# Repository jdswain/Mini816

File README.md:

# Mini816 (rev B)

This is the `v2` branch: rev B adds a floppy controller, moves the CPU
and flash to PLCC, drops TIM-Bus, and puts the external connectors along
the back edge for a case like the Atari ST (internal floppy drive and
keyboard). Rev A is on `main`.

A small 65C816 teaching computer: a gift kit for two first-year
computer science students. Through-hole parts throughout, for soldering
practice.

* W65C816S (PLCC-44 socket) at 7.3728 MHz, from a 14.7456 MHz oscillator
  divided in the CPLD
* 512K SRAM (AS6C4008-55) and 512K flash (SST39SF040, PLCC-32 socket): banks $00-$07
  RAM, $08-$0F flash. 128K parts fit the same sockets (see the Memory sheet
  for the RAM_SIZE jumper)
* ATF1504AS CPLD (PLCC-44 socket): bank latch, decode, strobes, clock
  generation and stretching for I/O cycles
* W65C22N VIA: 64-key keyboard on its own PCB (`../Mini816-Keyboard`),
  scanned through a 4-bit column select (PB0-PB2 + CA2) into a 74HC154 on
  the keyboard; Atari joystick (DE-9 on the keyboard PCB) on column 15; SD card over bit-banged SPI
  (microSD module); timer-1 sound; VDP interrupt on CB1, floppy interrupt on CB2
* Z85C30 SCC: two TTL serial ports on FTDI-style 6-pin headers; channel A
  takes a USB-C USB-serial module, which can also power the board
* TMS9118 video (NTSC composite, 256x192, 32 sprites) with two TMS4416
  VRAMs, driving a small composite LCD monitor
* Intel 82077AA floppy controller (PLCC-68 socket) at $C030, PC 34-pin
  drive header and 4-pin drive power header, for a 3.5" 720K/1.44M drive;
  no DMA (the CPU moves the data through the FIFO)
* 12 V barrel jack, metal toggle switch, Recom R-78K5.0-2.0 switching
  regulator (2 A, enough for the floppy drive) for 5 V; 12 V on a 2-pin header for the composite LCD. A jumper
  can instead take 5 V from the USB-serial module (bench use, no LCD)

All fine-pitch parts (USB, USB-serial chip, microSD socket) are on
plug-in modules, so the board itself is through-hole only.

Sheets: CPU, Memory, Logic, IO, Serial, Video, Floppy, Power. Each sheet
carries notes on its part of the design.

Symbols: `lib/65Parts.kicad_sym` is a copy of the 65-16 library;
`lib/Mini816.kicad_sym` holds the PLCC-44 and PDIP-40 W65C816S, W65C22 and Z85C30,
the TMS9118, TMS4416 and DS1813 (plus the now-unused ERM240128FS-2).

The CPLD pin assignment is on the Logic sheet; the Verilog must match it.

`docs/em16-profile.md` describes the machine for emulation (em16).

Board layout (rev B): 200 x 125 mm, 4 layers (inner 1 GND plane, inner 2
signals with a +5V pour). Back edge, left to right: 12 V jack, power
switch, LCD 12 V header, RCA video, SD module, serial A, serial B. Front
edge: keyboard ribbon header. Right edge: floppy drive header and drive
power. Four M3 mounting holes.

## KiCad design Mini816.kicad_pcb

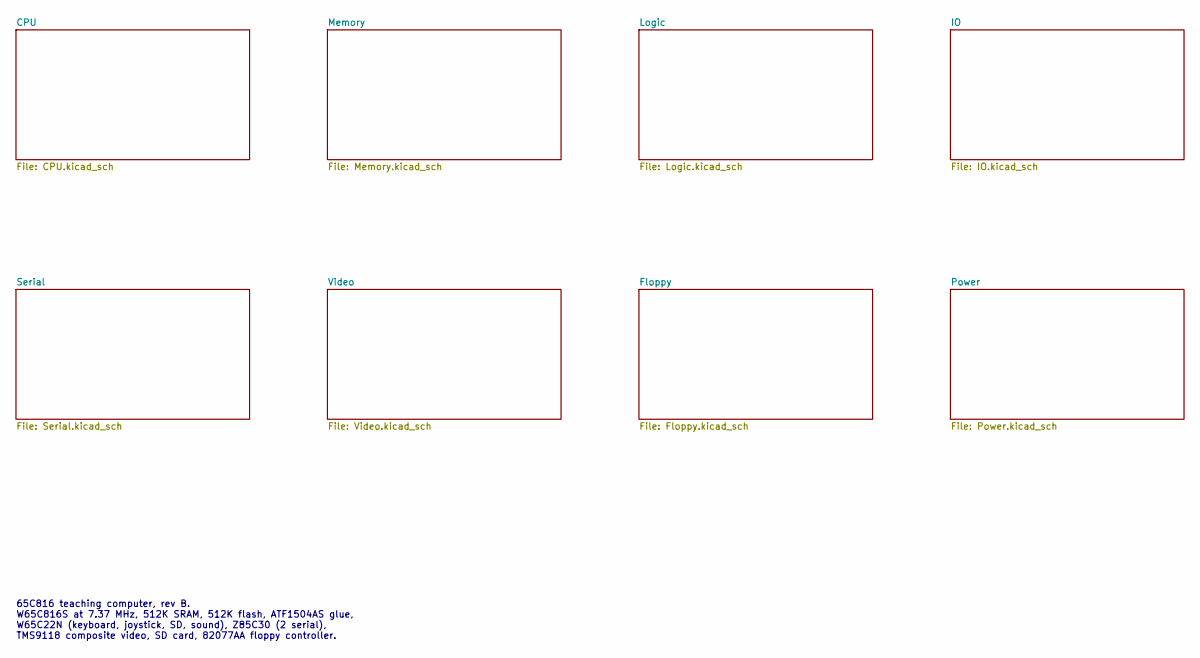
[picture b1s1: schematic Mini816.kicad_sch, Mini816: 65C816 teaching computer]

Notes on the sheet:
65C816 teaching computer, rev B. W65C816S at 7.37 MHz, 512K SRAM, 512K flash, ATF1504AS glue, W65C22N (keyboard, joystick, SD, sound), Z85C30 (2 serial), TMS9118 composite video, SD card, 82077AA floppy controller.

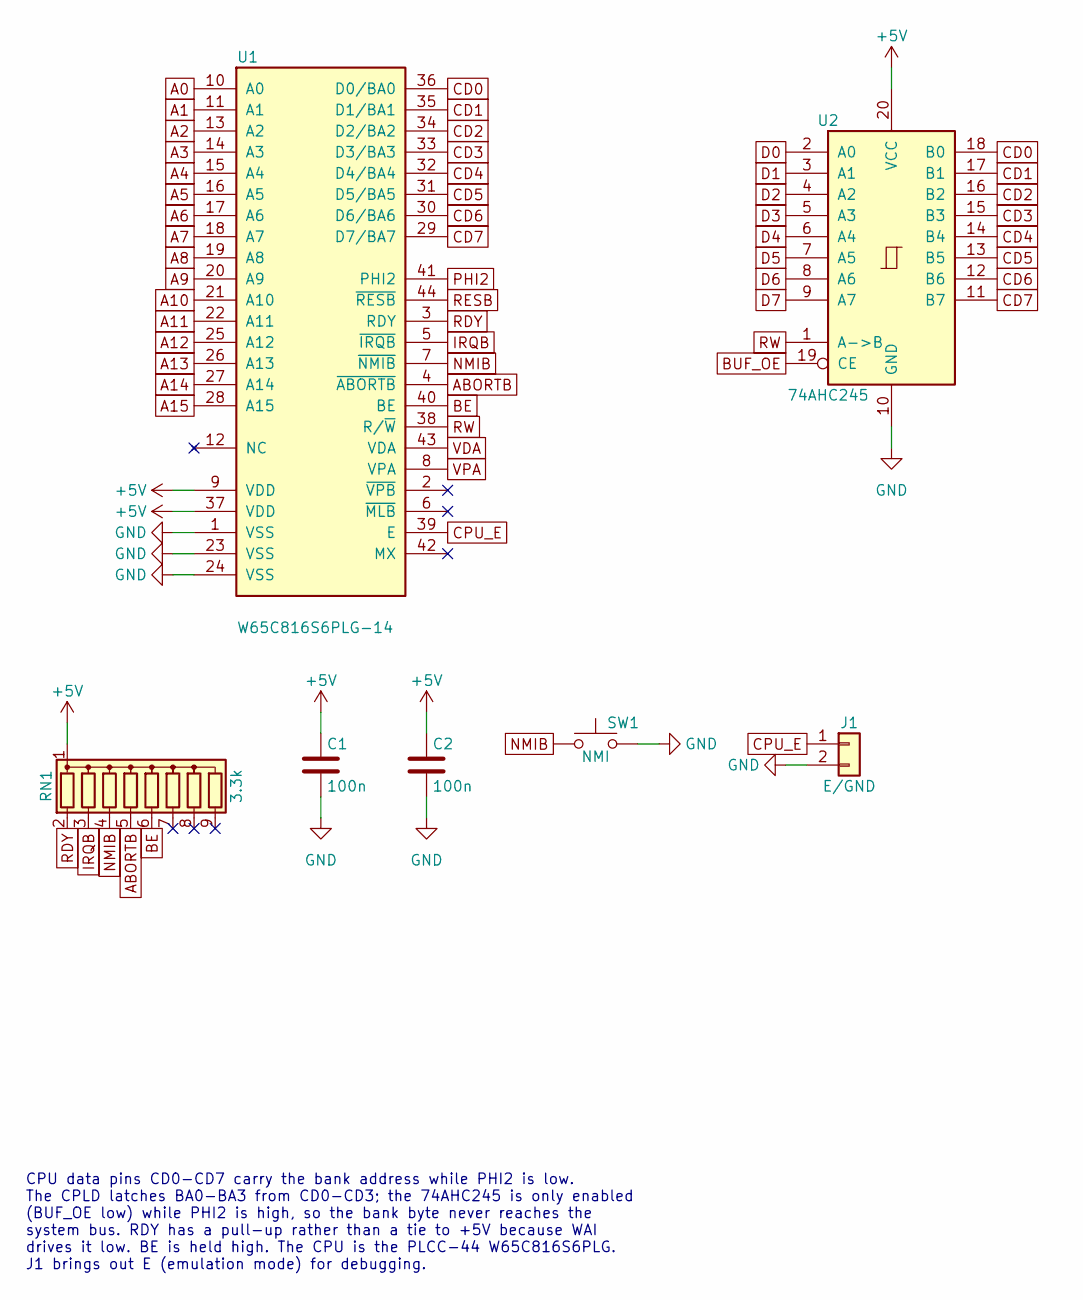
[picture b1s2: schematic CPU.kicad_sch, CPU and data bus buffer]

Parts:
C1, C2: 100n; C_Disc_D5.0mm_W2.5mm_P5.00mm
J1: E/GND; PinHeader_1x02_P2.54mm_Vertical
RN1: 3.3k; R_Array_SIP9
SW1: NMI; SW_PUSH_6mm
U1: W65C816S6PLG-14; PLCC-44_THT-Socket
U2: 74AHC245; DIP-20_W7.62mm_Socket

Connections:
+5V: C1.1, C2.1, RN1.1 (common), U1.9 (VDD), U1.37 (VDD), U2.20 (VCC); also elsewhere on the board
A0: U1.10 (A0); also elsewhere on the board
A1: U1.11 (A1); also elsewhere on the board
A2: U1.13 (A2); also elsewhere on the board
A3: U1.14 (A3); also elsewhere on the board
A4: U1.15 (A4); also elsewhere on the board
A5: U1.16 (A5); also elsewhere on the board
A6: U1.17 (A6); also elsewhere on the board
A7: U1.18 (A7); also elsewhere on the board
A8: U1.19 (A8); also elsewhere on the board
A9: U1.20 (A9); also elsewhere on the board
A10: U1.21 (A10); also elsewhere on the board
A11: U1.22 (A11); also elsewhere on the board
A12: U1.25 (A12); also elsewhere on the board
A13: U1.26 (A13); also elsewhere on the board
A14: U1.27 (A14); also elsewhere on the board
A15: U1.28 (A15); also elsewhere on the board
ABORTB: RN1.5 (R4), U1.4 (~ABORTB)
BE: RN1.6 (R5), U1.40 (BE)
BUF_OE: U2.19 (CE); also elsewhere on the board
CD0: U1.36 (D0/BA0), U2.18 (B0); also elsewhere on the board
CD1: U1.35 (D1/BA1), U2.17 (B1); also elsewhere on the board
CD2: U1.34 (D2/BA2), U2.16 (B2); also elsewhere on the board
CD3: U1.33 (D3/BA3), U2.15 (B3); also elsewhere on the board
CD4: U1.32 (D4/BA4), U2.14 (B4)
CD5: U1.31 (D5/BA5), U2.13 (B5)
CD6: U1.30 (D6/BA6), U2.12 (B6)
CD7: U1.29 (D7/BA7), U2.11 (B7)
CPU_E: J1.1, U1.39 (E)
D0: U2.2 (A0); also elsewhere on the board
D1: U2.3 (A1); also elsewhere on the board
D2: U2.4 (A2); also elsewhere on the board
D3: U2.5 (A3); also elsewhere on the board
D4: U2.6 (A4); also elsewhere on the board
D5: U2.7 (A5); also elsewhere on the board
D6: U2.8 (A6); also elsewhere on the board
D7: U2.9 (A7); also elsewhere on the board
GND: C1.2, C2.2, J1.2, SW1.2, U1.1 (VSS), U1.23 (VSS), U1.24 (VSS), U2.10 (GND); also elsewhere on the board
IRQB: RN1.3 (R2), U1.5 (~IRQB); also elsewhere on the board
NMIB: RN1.4 (R3), SW1.1, U1.7 (~NMIB)
PHI2: U1.41 (PHI2); also elsewhere on the board
RDY: RN1.2 (R1), U1.3 (RDY)
RESB: U1.44 (~RESB); also elsewhere on the board
RW: U1.38 (R/~W), U2.1 (A->B); also elsewhere on the board
VDA: U1.43 (VDA); also elsewhere on the board
VPA: U1.8 (VPA); also elsewhere on the board

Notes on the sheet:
CPU data pins CD0-CD7 carry the bank address while PHI2 is low. The CPLD latches BA0-BA3 from CD0-CD3; the 74AHC245 is only enabled (BUF_OE low) while PHI2 is high, so the bank byte never reaches the system bus. RDY has a pull-up rather than a tie to +5V because WAI drives it low. BE is held high. 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

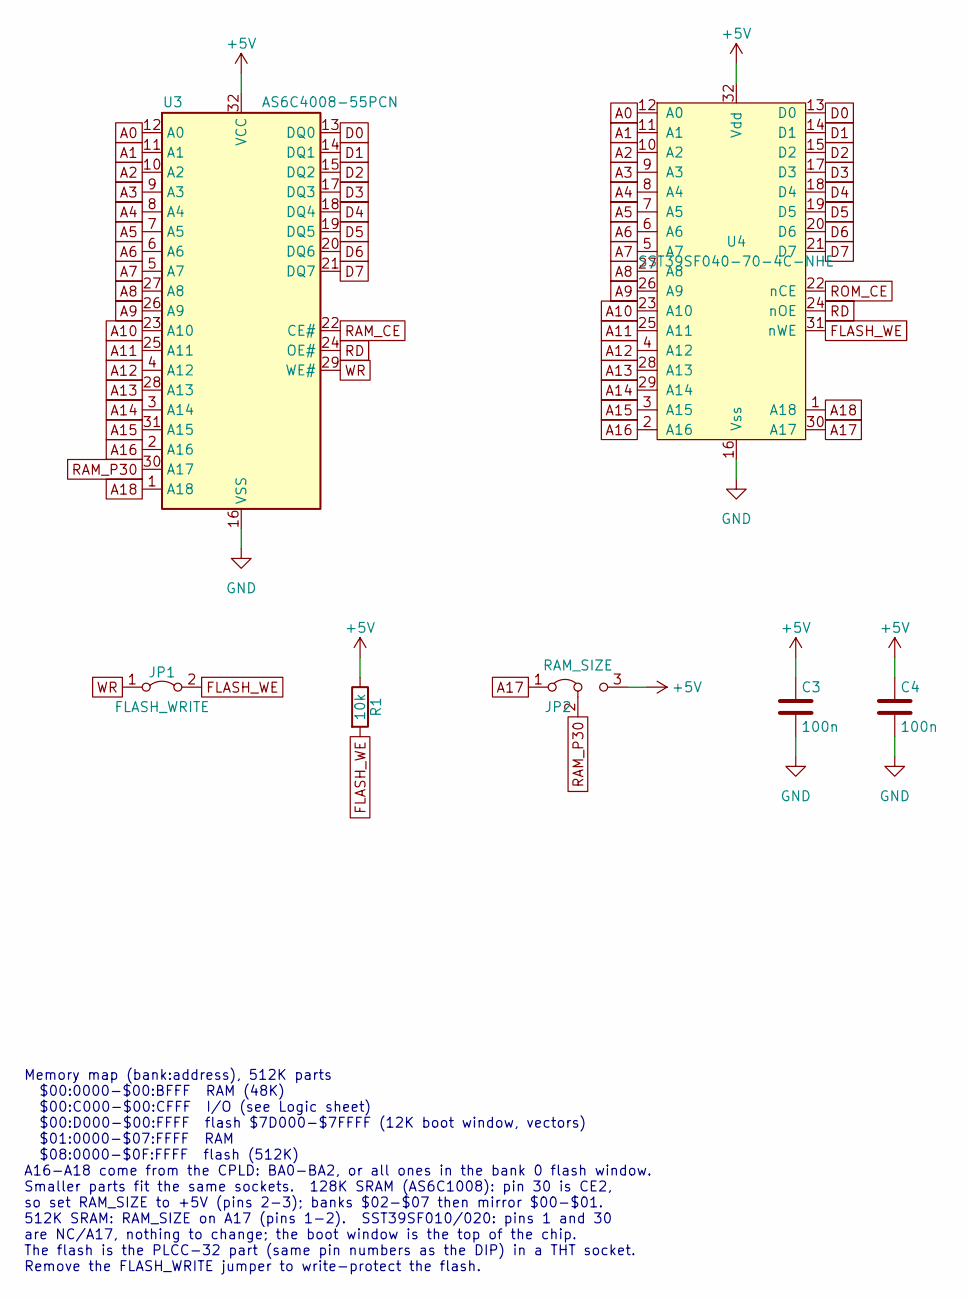
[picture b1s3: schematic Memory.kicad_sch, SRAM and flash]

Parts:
C3, C4: 100n; C_Disc_D5.0mm_W2.5mm_P5.00mm
JP1: FLASH_WRITE; PinHeader_1x02_P2.54mm_Vertical
JP2: RAM_SIZE; PinHeader_1x03_P2.54mm_Vertical
R1: 10k; R_Axial_DIN0207_L6.3mm_D2.5mm_P10.16mm_Horizontal
U3: AS6C4008-55PCN; DIP-32_W15.24mm_Socket
U4: SST39SF040-70-4C-NHE; PLCC-32_THT-Socket

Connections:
+5V: C3.1, C4.1, JP2.3 (B), R1.1, U3.32 (VCC), U4.32 (Vdd); also elsewhere on the board
A0: U3.12 (A0), U4.12 (A0); also elsewhere on the board
A1: U3.11 (A1), U4.11 (A1); also elsewhere on the board
A2: U3.10 (A2), U4.10 (A2); also elsewhere on the board
A3: U3.9 (A3), U4.9 (A3); also elsewhere on the board
A4: U3.8 (A4), U4.8 (A4); also elsewhere on the board
A5: U3.7 (A5), U4.7 (A5); also elsewhere on the board
A6: U3.6 (A6), U4.6 (A6); also elsewhere on the board
A7: U3.5 (A7), U4.5 (A7); also elsewhere on the board
A8: U3.27 (A8), U4.27 (A8); also elsewhere on the board
A9: U3.26 (A9), U4.26 (A9); also elsewhere on the board
A10: U3.23 (A10), U4.23 (A10); also elsewhere on the board
A11: U3.25 (A11), U4.25 (A11); also elsewhere on the board
A12: U3.4 (A12), U4.4 (A12); also elsewhere on the board
A13: U3.28 (A13), U4.28 (A13); also elsewhere on the board
A14: U3.3 (A14), U4.29 (A14); also elsewhere on the board
A15: U3.31 (A15), U4.3 (A15); also elsewhere on the board
A16: U3.2 (A16), U4.2 (A16); also elsewhere on the board
A17: JP2.1 (A), U4.30 (A17); also elsewhere on the board
A18: U3.1 (A18), U4.1 (A18); also elsewhere on the board
D0: U3.13 (DQ0), U4.13 (D0); also elsewhere on the board
D1: U3.14 (DQ1), U4.14 (D1); also elsewhere on the board
D2: U3.15 (DQ2), U4.15 (D2); also elsewhere on the board
D3: U3.17 (DQ3), U4.17 (D3); also elsewhere on the board
D4: U3.18 (DQ4), U4.18 (D4); also elsewhere on the board
D5: U3.19 (DQ5), U4.19 (D5); also elsewhere on the board
D6: U3.20 (DQ6), U4.20 (D6); also elsewhere on the board
D7: U3.21 (DQ7), U4.21 (D7); also elsewhere on the board
FLASH_WE: JP1.2 (B), R1.2, U4.31 (nWE)
GND: C3.2, C4.2, U3.16 (VSS), U4.16 (Vss); also elsewhere on the board
RAM_CE: U3.22 (CE#); also elsewhere on the board
RAM_P30: JP2.2 (C), U3.30 (A17)
RD: U3.24 (OE#), U4.24 (nOE); also elsewhere on the board
ROM_CE: U4.22 (nCE); also elsewhere on the board
WR: JP1.1 (A), U3.29 (WE#); also elsewhere on the board

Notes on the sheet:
Memory map (bank:address), 512K parts $00:0000-$00:BFFF RAM (48K) $00:C000-$00:CFFF I/O (see Logic sheet) $00:D000-$00:FFFF flash $7D000-$7FFFF (12K boot window, vectors) $01:0000-$07:FFFF RAM $08:0000-$0F:FFFF flash (512K) A16-A18 come from the CPLD: BA0-BA2, or all ones in the bank 0 flash window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

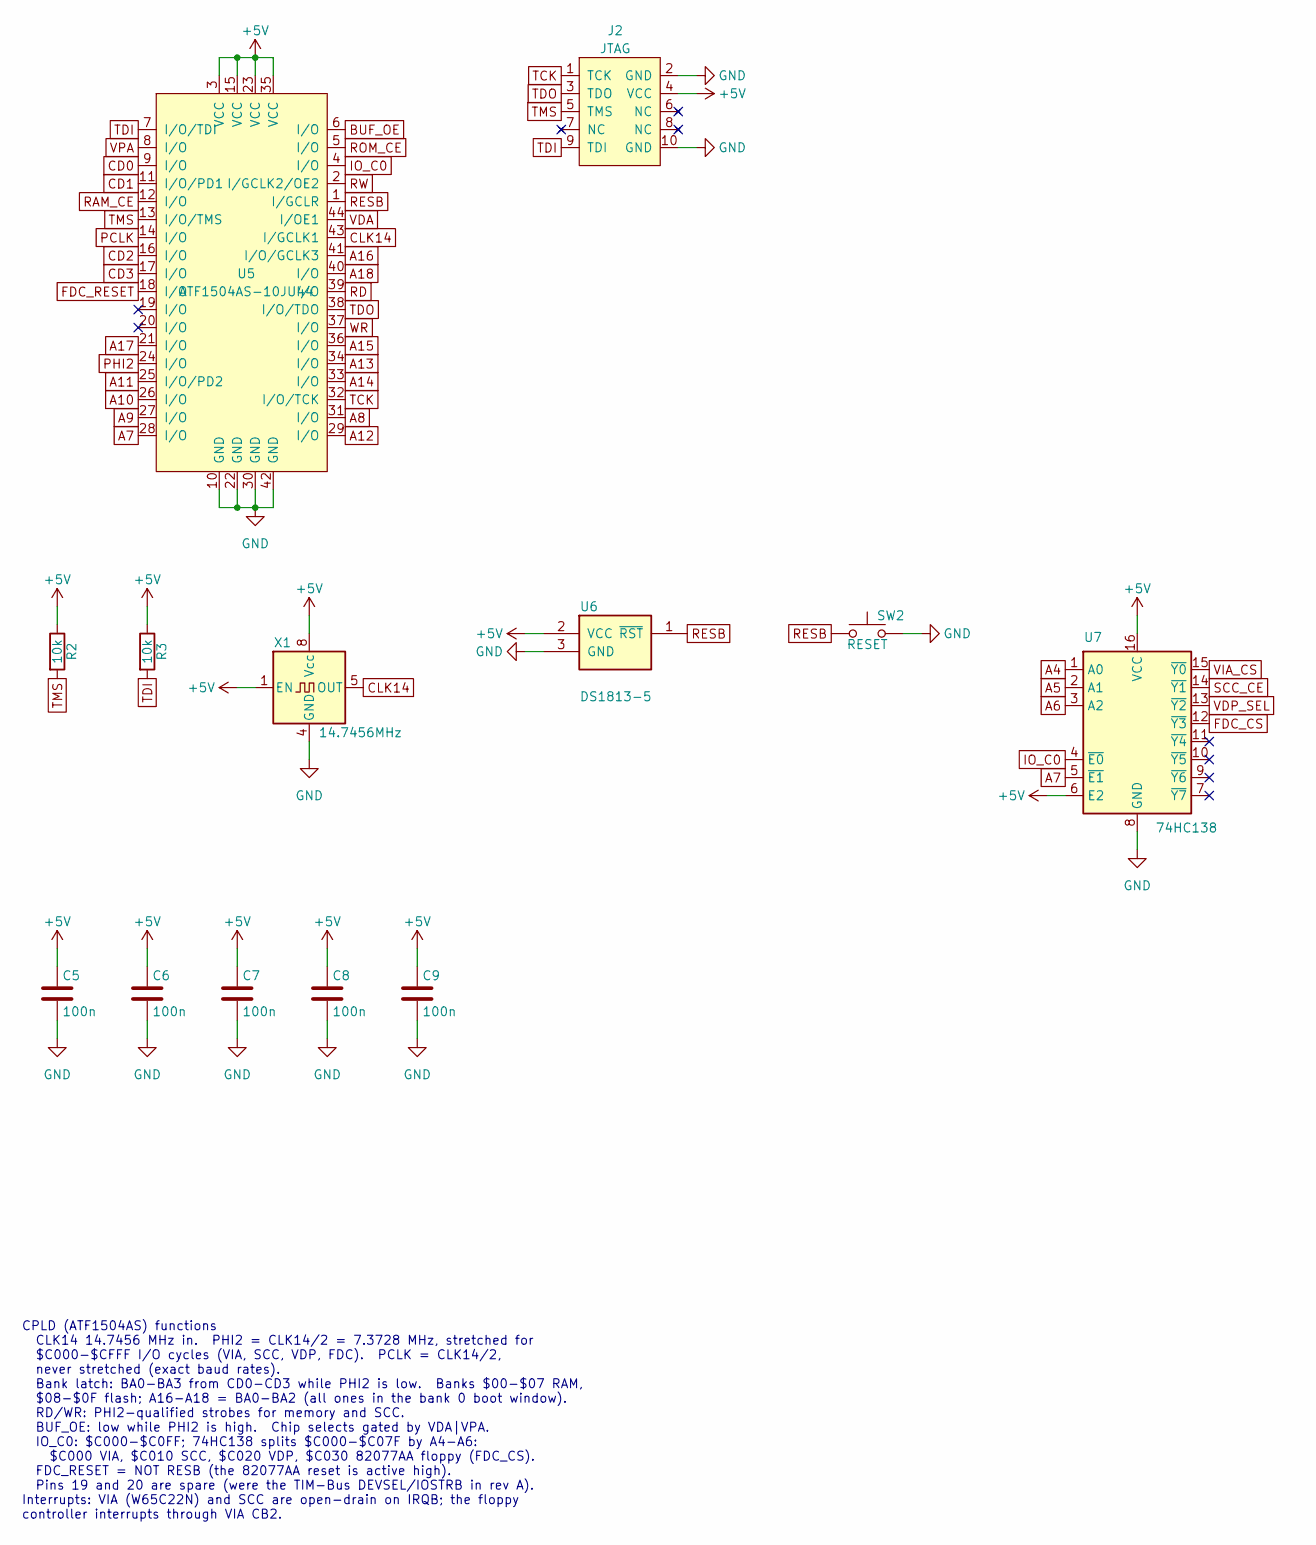
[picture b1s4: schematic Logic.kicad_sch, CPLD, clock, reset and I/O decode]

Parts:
C5, C6, C7, C8, C9: 100n; C_Disc_D5.0mm_W2.5mm_P5.00mm
J2: JTAG; IDC-Header_2x05_P2.54mm_Vertical
R2, R3: 10k; R_Axial_DIN0207_L6.3mm_D2.5mm_P10.16mm_Horizontal
SW2: RESET; SW_PUSH_6mm
U5: ATF1504AS-10JU44; PLCC-44_THT-Socket
U6: DS1813-5; TO-92_Inline_Wide
U7: 74HC138; DIP-16_W7.62mm_Socket
X1: 14.7456MHz; Oscillator_DIP-8

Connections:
+5V: C5.1, C6.1, C7.1, C8.1, C9.1, J2.4 (VCC), R2.1, R3.1, U5.3 (VCC), U5.15 (VCC), U5.23 (VCC), U5.35 (VCC), U6.2 (VCC), U7.6 (E2), U7.16 (VCC), X1.1 (EN), X1.8 (Vcc); also elsewhere on the board
A4: U7.1 (A0); also elsewhere on the board
A5: U7.2 (A1); also elsewhere on the board
A6: U7.3 (A2); also elsewhere on the board
A7: U5.28 (I/O), U7.5 (~E1); also elsewhere on the board
A8: U5.31 (I/O); also elsewhere on the board
A9: U5.27 (I/O); also elsewhere on the board
A10: U5.26 (I/O); also elsewhere on the board
A11: U5.25 (I/O/PD2); also elsewhere on the board
A12: U5.29 (I/O); also elsewhere on the board
A13: U5.34 (I/O); also elsewhere on the board
A14: U5.33 (I/O); also elsewhere on the board
A15: U5.36 (I/O); also elsewhere on the board
A16: U5.41 (I/O/GCLK3); also elsewhere on the board
A17: U5.21 (I/O); also elsewhere on the board
A18: U5.40 (I/O); also elsewhere on the board
BUF_OE: U5.6 (I/O); also elsewhere on the board
CD0: U5.9 (I/O); also elsewhere on the board
CD1: U5.11 (I/O/PD1); also elsewhere on the board
CD2: U5.16 (I/O); also elsewhere on the board
CD3: U5.17 (I/O); also elsewhere on the board
CLK14: U5.43 (I/GCLK1), X1.5 (OUT)
FDC_CS: U7.12 (~Y3); also elsewhere on the board
FDC_RESET: U5.18 (I/O); also elsewhere on the board
GND: C5.2, C6.2, C7.2, C8.2, C9.2, J2.2 (GND), J2.10 (GND), SW2.2, U5.10 (GND), U5.22 (GND), U5.30 (GND), U5.42 (GND), U6.3 (GND), U7.8 (GND), X1.4 (GND); also elsewhere on the board
IO_C0: U5.4 (I/O), U7.4 (~E0)
PCLK: U5.14 (I/O); also elsewhere on the board
PHI2: U5.24 (I/O); also elsewhere on the board
RAM_CE: U5.12 (I/O); also elsewhere on the board
RD: U5.39 (I/O); also elsewhere on the board
RESB: SW2.1, U5.1 (I/GCLR), U6.1 (~RST); also elsewhere on the board
ROM_CE: U5.5 (I/O); also elsewhere on the board
RW: U5.2 (I/GCLK2/OE2); also elsewhere on the board
SCC_CE: U7.14 (~Y1); also elsewhere on the board
TCK: J2.1 (TCK), U5.32 (I/O/TCK)
TDI: J2.9 (TDI), R3.2, U5.7 (I/O/TDI)
TDO: J2.3 (TDO), U5.38 (I/O/TDO)
TMS: J2.5 (TMS), R2.2, U5.13 (I/O/TMS)
VDA: U5.44 (I/OE1); also elsewhere on the board
VDP_SEL: U7.13 (~Y2); also elsewhere on the board
VIA_CS: U7.15 (~Y0); also elsewhere on the board
VPA: U5.8 (I/O); also elsewhere on the board
WR: U5.37 (I/O); also elsewhere on the board

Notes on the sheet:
CPLD (ATF1504AS) functions CLK14 14.7456 MHz in. PHI2 = CLK14/2 = 7.3728 MHz, stretched for $C000-$CFFF I/O cycles (VIA, SCC, VDP, FDC). PCLK = CLK14/2, never stretched (exact baud rates). Bank latch: BA0-BA3 from CD0-CD3 while PHI2 is low. Banks $00-$07 RAM, $08-$0F flash; A16-A18 = BA0-BA2 (all o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

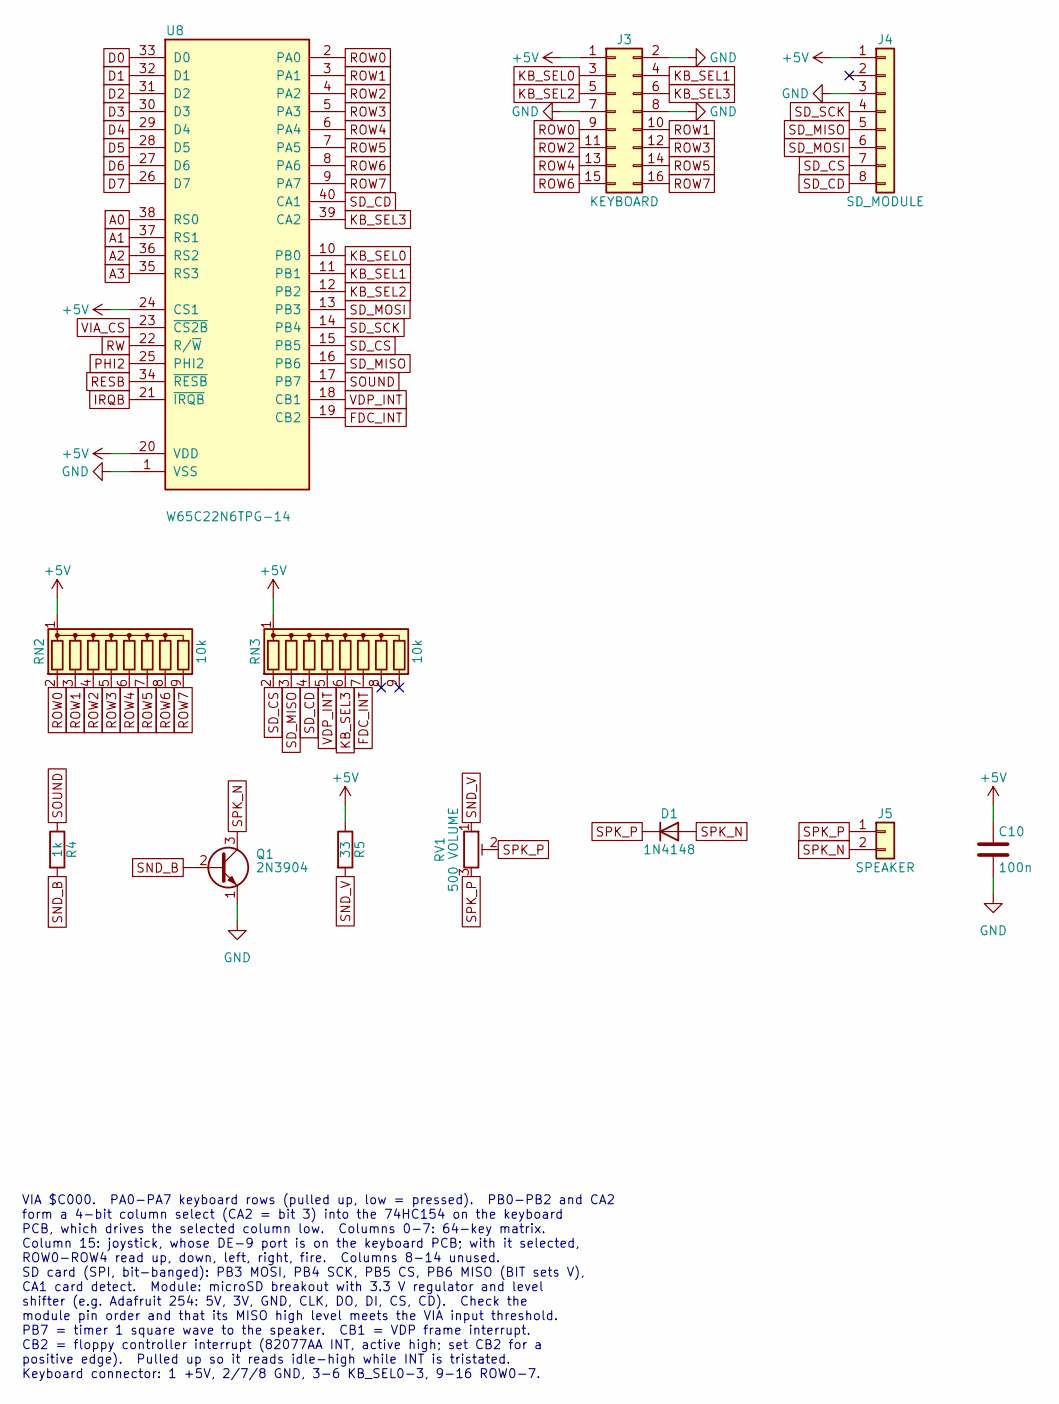
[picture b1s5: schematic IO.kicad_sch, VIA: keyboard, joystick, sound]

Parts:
C10: 100n; C_Disc_D5.0mm_W2.5mm_P5.00mm
D1: 1N4148; D_DO-35_SOD27_P7.62mm_Horizontal
J3: KEYBOARD; IDC-Header_2x08_P2.54mm_Vertical
J4: SD_MODULE; PinSocket_1x08_P2.54mm_Vertical
J5: SPEAKER; PinHeader_1x02_P2.54mm_Vertical
Q1: 2N3904; TO-92_Inline_Wide
R4: 1k; R_Axial_DIN0207_L6.3mm_D2.5mm_P10.16mm_Horizontal
R5: 33; R_Axial_DIN0207_L6.3mm_D2.5mm_P10.16mm_Horizontal
RN2, RN3: 10k; R_Array_SIP9
RV1: 500 VOLUME; Potentiometer_Bourns_3296W_Vertical
U8: W65C22N6TPG-14; DIP-40_W15.24mm_Socket

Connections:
+5V: C10.1, J3.1, J4.1, R5.1, RN2.1 (common), RN3.1 (common), U8.20 (VDD), U8.24 (CS1); also elsewhere on the board
A0: U8.38 (RS0); also elsewhere on the board
A1: U8.37 (RS1); also elsewhere on the board
A2: U8.36 (RS2); also elsewhere on the board
A3: U8.35 (RS3); also elsewhere on the board
D0: U8.33 (D0); also elsewhere on the board
D1: U8.32 (D1); also elsewhere on the board
D2: U8.31 (D2); also elsewhere on the board
D3: U8.30 (D3); also elsewhere on the board
D4: U8.29 (D4); also elsewhere on the board
D5: U8.28 (D5); also elsewhere on the board
D6: U8.27 (D6); also elsewhere on the board
D7: U8.26 (D7); also elsewhere on the board
FDC_INT: RN3.7 (R6), U8.19 (CB2); also elsewhere on the board
GND: C10.2, J3.2, J3.7, J3.8, J4.3, Q1.1 (E), U8.1 (VSS); also elsewhere on the board
IRQB: U8.21 (~IRQB); also elsewhere on the board
KB_SEL0: J3.3, U8.10 (PB0)
KB_SEL1: J3.4, U8.11 (PB1)
KB_SEL2: J3.5, U8.12 (PB2)
KB_SEL3: J3.6, RN3.6 (R5), U8.39 (CA2)
PHI2: U8.25 (PHI2); also elsewhere on the board
RESB: U8.34 (~RESB); also elsewhere on the board
ROW0: J3.9, RN2.2 (R1), U8.2 (PA0)
ROW1: J3.10, RN2.3 (R2), U8.3 (PA1)
ROW2: J3.11, RN2.4 (R3), U8.4 (PA2)
ROW3: J3.12, RN2.5 (R4), U8.5 (PA3)
ROW4: J3.13, RN2.6 (R5), U8.6 (PA4)
ROW5: J3.14, RN2.7 (R6), U8.7 (PA5)
ROW6: J3.15, RN2.8 (R7), U8.8 (PA6)
ROW7: J3.16, RN2.9 (R8), U8.9 (PA7)
RW: U8.22 (R/~W); also elsewhere on the board
SD_CD: J4.8, RN3.4 (R3), U8.40 (CA1)
SD_CS: J4.7, RN3.2 (R1), U8.15 (PB5)
SD_MISO: J4.5, RN3.3 (R2), U8.16 (PB6)
SD_MOSI: J4.6, U8.13 (PB3)
SD_SCK: J4.4, U8.14 (PB4)
SND_B: Q1.2 (B), R4.2
SND_V: R5.2, RV1.1
SOUND: R4.1, U8.17 (PB7)
SPK_N: D1.2 (A), J5.2, Q1.3 (C)
SPK_P: D1.1 (K), J5.1, RV1.2, RV1.3
VDP_INT: RN3.5 (R4), U8.18 (CB1); also elsewhere on the board
VIA_CS: U8.23 (~CS2B); also elsewhere on the board

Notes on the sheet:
VIA $C000. PA0-PA7 keyboard rows (pulled up, low = pressed). PB0-PB2 and CA2 form a 4-bit column select (CA2 = bit 3) into the 74HC154 on the keyboard PCB, which drives the selected column low. Columns 0-7: 64-key matrix. Column 15: joystick, whose DE-9 port is on the keyboard PCB; with it selected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

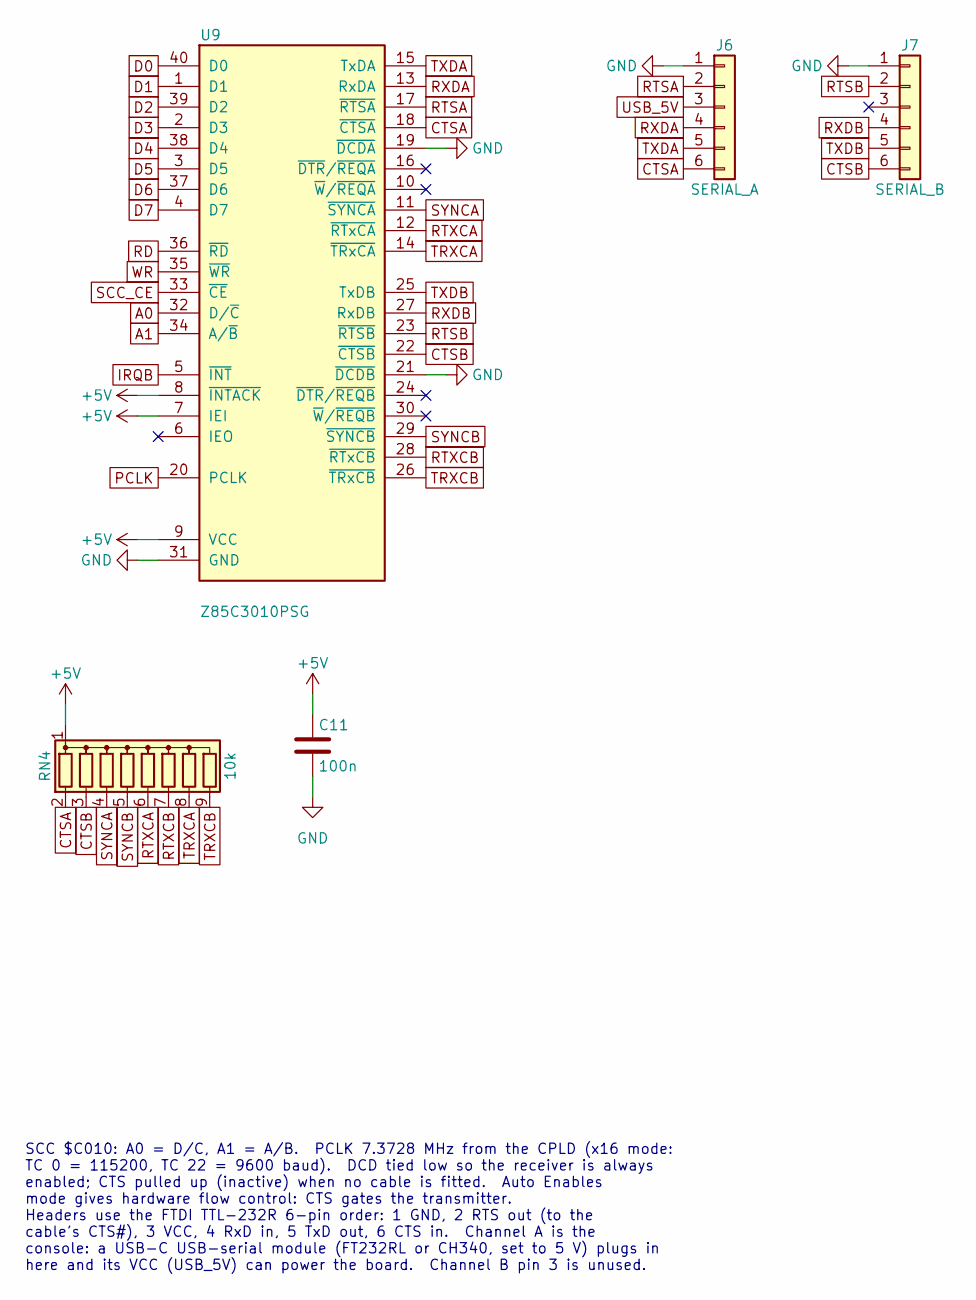
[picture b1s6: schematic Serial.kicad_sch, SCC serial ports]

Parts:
C11: 100n; C_Disc_D5.0mm_W2.5mm_P5.00mm
J6: SERIAL_A; PinHeader_1x06_P2.54mm_Vertical
J7: SERIAL_B; PinHeader_1x06_P2.54mm_Vertical
RN4: 10k; R_Array_SIP9
U9: Z85C3010PSG; DIP-40_W15.24mm_Socket

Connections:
+5V: C11.1, RN4.1 (common), U9.7 (IEI), U9.8 (~INTACK), U9.9 (VCC); also elsewhere on the board
A0: U9.32 (D/~C); also elsewhere on the board
A1: U9.34 (A/~B); also elsewhere on the board
CTSA: J6.6, RN4.2 (R1), U9.18 (~CTSA)
CTSB: J7.6, RN4.3 (R2), U9.22 (~CTSB)
D0: U9.40 (D0); also elsewhere on the board
D1: U9.1 (D1); also elsewhere on the board
D2: U9.39 (D2); also elsewhere on the board
D3: U9.2 (D3); also elsewhere on the board
D4: U9.38 (D4); also elsewhere on the board
D5: U9.3 (D5); also elsewhere on the board
D6: U9.37 (D6); also elsewhere on the board
D7: U9.4 (D7); also elsewhere on the board
GND: C11.2, J6.1, J7.1, U9.19 (~DCDA), U9.21 (~DCDB), U9.31 (GND); also elsewhere on the board
IRQB: U9.5 (~INT); also elsewhere on the board
PCLK: U9.20 (PCLK); also elsewhere on the board
RD: U9.36 (~RD); also elsewhere on the board
RTSA: J6.2, U9.17 (~RTSA)
RTSB: J7.2, U9.23 (~RTSB)
RTXCA: RN4.6 (R5), U9.12 (~RTxCA)
RTXCB: RN4.7 (R6), U9.28 (~RTxCB)
RXDA: J6.4, U9.13 (RxDA)
RXDB: J7.4, U9.27 (RxDB)
SCC_CE: U9.33 (~CE); also elsewhere on the board
SYNCA: RN4.4 (R3), U9.11 (~SYNCA)
SYNCB: RN4.5 (R4), U9.29 (~SYNCB)
TRXCA: RN4.8 (R7), U9.14 (~TRxCA)
TRXCB: RN4.9 (R8), U9.26 (~TRxCB)
TXDA: J6.5, U9.15 (TxDA)
TXDB: J7.5, U9.25 (TxDB)
USB_5V: J6.3; also elsewhere on the board
WR: U9.35 (~WR); also elsewhere on the board

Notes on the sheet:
SCC $C010: A0 = D/C, A1 = A/B. PCLK 7.3728 MHz from the CPLD (x16 mode: TC 0 = 115200, TC 22 = 9600 baud). DCD tied low so the receiver is always enabled; CTS pulled up (inactive) when no cable is fitted. Auto Enables mode gives hardware flow control: CTS gates the transmitter. Headers use the FTDI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

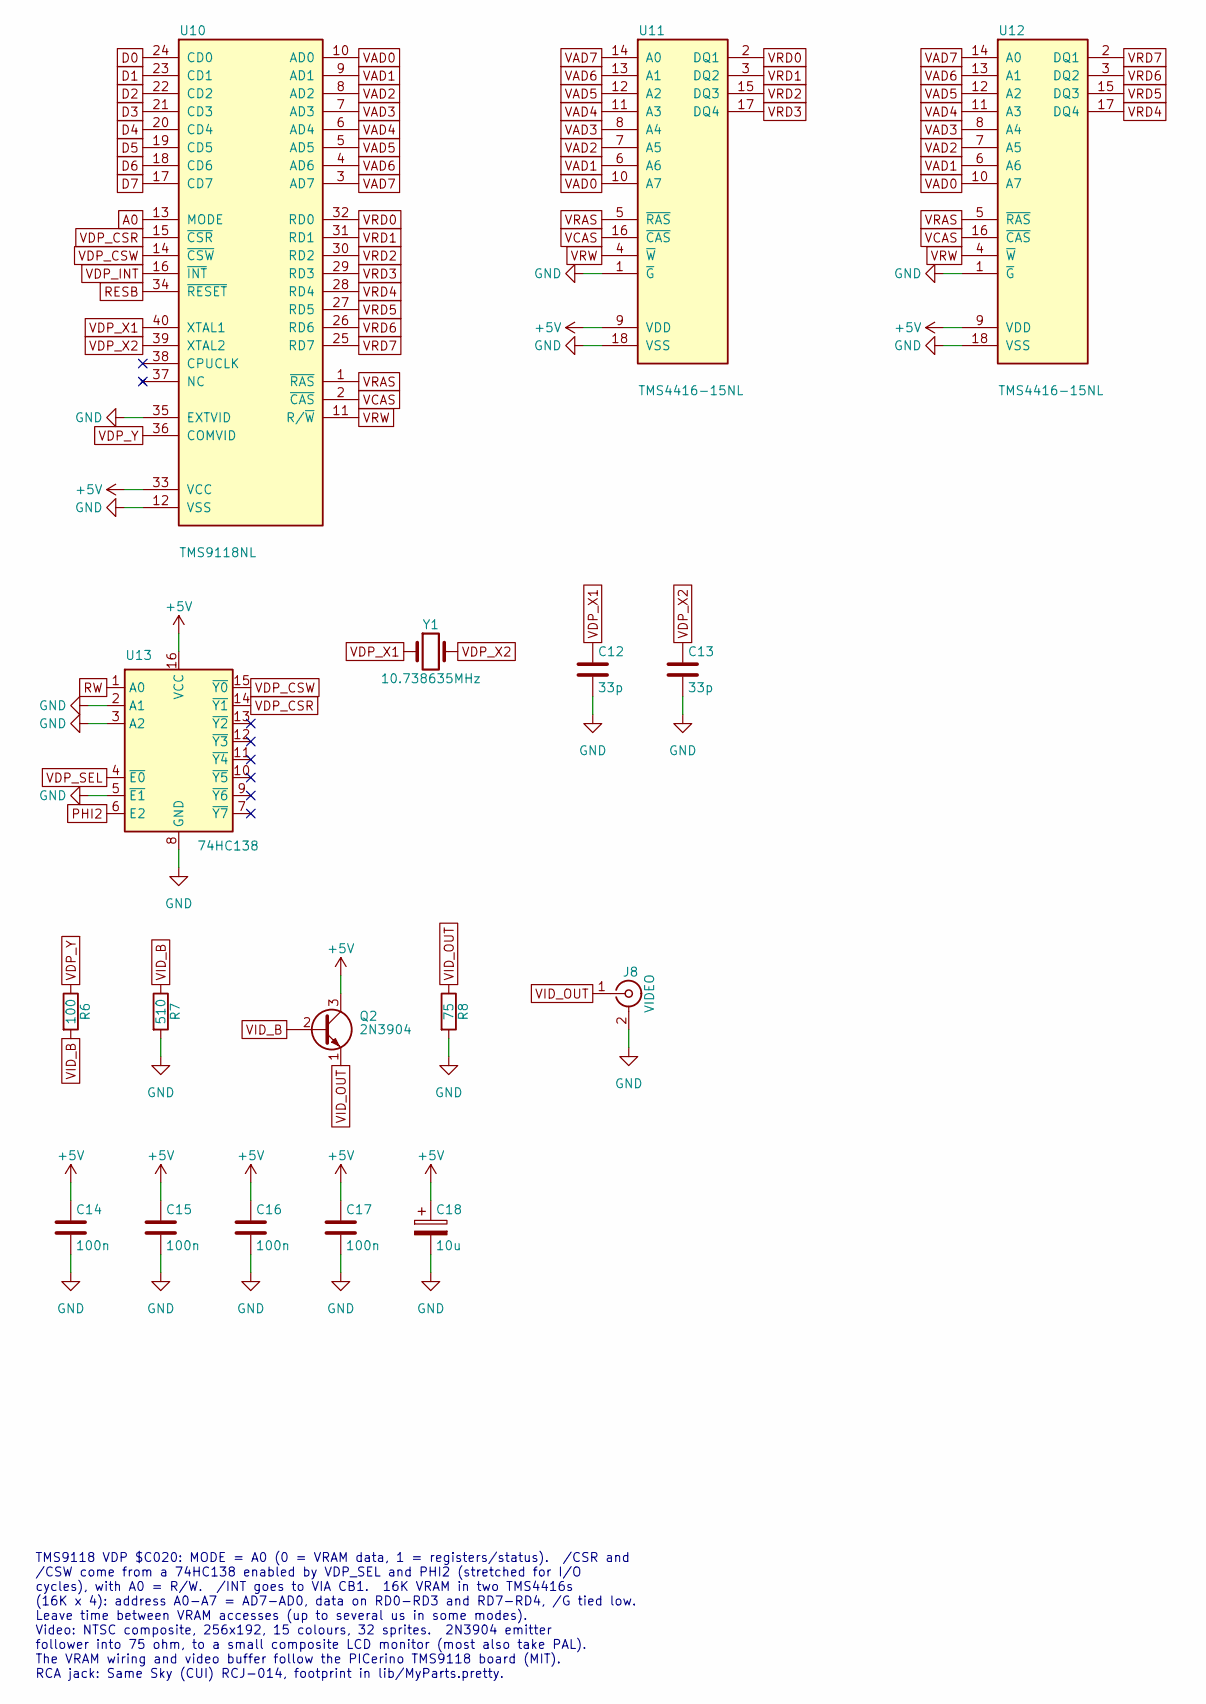
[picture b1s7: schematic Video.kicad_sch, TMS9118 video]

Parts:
C12, C13: 33p; C_Disc_D5.0mm_W2.5mm_P5.00mm
C14, C15, C16, C17: 100n; C_Disc_D5.0mm_W2.5mm_P5.00mm
C18: 10u; CP_Radial_D6.3mm_P2.50mm
J8: VIDEO; RCA_SameSky_RCJ-01x_Horizontal; MPN Same Sky RCJ-014 (yellow)
Q2: 2N3904; TO-92_Inline_Wide
R6: 100; R_Axial_DIN0207_L6.3mm_D2.5mm_P10.16mm_Horizontal
R7: 510; R_Axial_DIN0207_L6.3mm_D2.5mm_P10.16mm_Horizontal
R8: 75; R_Axial_DIN0207_L6.3mm_D2.5mm_P10.16mm_Horizontal
U10: TMS9118NL; DIP-40_W15.24mm_Socket
U11, U12: TMS4416-15NL; DIP-18_W7.62mm_Socket
U13: 74HC138; DIP-16_W7.62mm_Socket
Y1: 10.738635MHz; Crystal_HC49-4H_Vertical

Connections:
+5V: C14.1, C15.1, C16.1, C17.1, C18.1, Q2.3 (C), U10.33 (VCC), U11.9 (VDD), U12.9 (VDD), U13.16 (VCC); also elsewhere on the board
A0: U10.13 (MODE); also elsewhere on the board
D0: U10.24 (CD0); also elsewhere on the board
D1: U10.23 (CD1); also elsewhere on the board
D2: U10.22 (CD2); also elsewhere on the board
D3: U10.21 (CD3); also elsewhere on the board
D4: U10.20 (CD4); also elsewhere on the board
D5: U10.19 (CD5); also elsewhere on the board
D6: U10.18 (CD6); also elsewhere on the board
D7: U10.17 (CD7); also elsewhere on the board
GND: C12.2, C13.2, C14.2, C15.2, C16.2, C17.2, C18.2, J8.2 (Ext), R7.2, R8.2, U10.12 (VSS), U10.35 (EXTVID), U11.1 (~G), U11.18 (VSS), U12.1 (~G), U12.18 (VSS), U13.2 (A1), U13.3 (A2), U13.5 (~E1), U13.8 (GND); also elsewhere on the board
PHI2: U13.6 (E2); also elsewhere on the board
RESB: U10.34 (~RESET); also elsewhere on the board
RW: U13.1 (A0); also elsewhere on the board
VAD0: U10.10 (AD0), U11.10 (A7), U12.10 (A7)
VAD1: U10.9 (AD1), U11.6 (A6), U12.6 (A6)
VAD2: U10.8 (AD2), U11.7 (A5), U12.7 (A5)
VAD3: U10.7 (AD3), U11.8 (A4), U12.8 (A4)
VAD4: U10.6 (AD4), U11.11 (A3), U12.11 (A3)
VAD5: U10.5 (AD5), U11.12 (A2), U12.12 (A2)
VAD6: U10.4 (AD6), U11.13 (A1), U12.13 (A1)
VAD7: U10.3 (AD7), U11.14 (A0), U12.14 (A0)
VCAS: U10.2 (~CAS), U11.16 (~CAS), U12.16 (~CAS)
VDP_CSR: U10.15 (~CSR), U13.14 (~Y1)
VDP_CSW: U10.14 (~CSW), U13.15 (~Y0)
VDP_INT: U10.16 (~INT); also elsewhere on the board
VDP_SEL: U13.4 (~E0); also elsewhere on the board
VDP_X1: C12.1, U10.40 (XTAL1), Y1.1
VDP_X2: C13.1, U10.39 (XTAL2), Y1.2
VDP_Y: R6.1, U10.36 (COMVID)
VID_B: Q2.2 (B), R6.2, R7.1
VID_OUT: J8.1 (In), Q2.1 (E), R8.1
VRAS: U10.1 (~RAS), U11.5 (~RAS), U12.5 (~RAS)
VRD0: U10.32 (RD0), U11.2 (DQ1)
VRD1: U10.31 (RD1), U11.3 (DQ2)
VRD2: U10.30 (RD2), U11.15 (DQ3)
VRD3: U10.29 (RD3), U11.17 (DQ4)
VRD4: U10.28 (RD4), U12.17 (DQ4)
VRD5: U10.27 (RD5), U12.15 (DQ3)
VRD6: U10.26 (RD6), U12.3 (DQ2)
VRD7: U10.25 (RD7), U12.2 (DQ1)
VRW: U10.11 (R/~W), U11.4 (~W), U12.4 (~W)

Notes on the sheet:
TMS9118 VDP $C020: MODE = A0 (0 = VRAM data, 1 = registers/status). /CSR and /CSW come from a 74HC138 enabled by VDP_SEL and PHI2 (stretched for I/O cycles), with A0 = R/W. /INT goes to VIA CB1. 16K VRAM in two TMS4416s (16K x 4): address A0-A7 = AD7-AD0, data on RD0-RD3 and RD7-RD4, /G tied low. L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
